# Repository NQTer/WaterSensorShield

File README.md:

# WaterSensorShield
RFM69 and ESP8266-01 enabled Water Level/Leak Detation Arduino Shield (Tested)

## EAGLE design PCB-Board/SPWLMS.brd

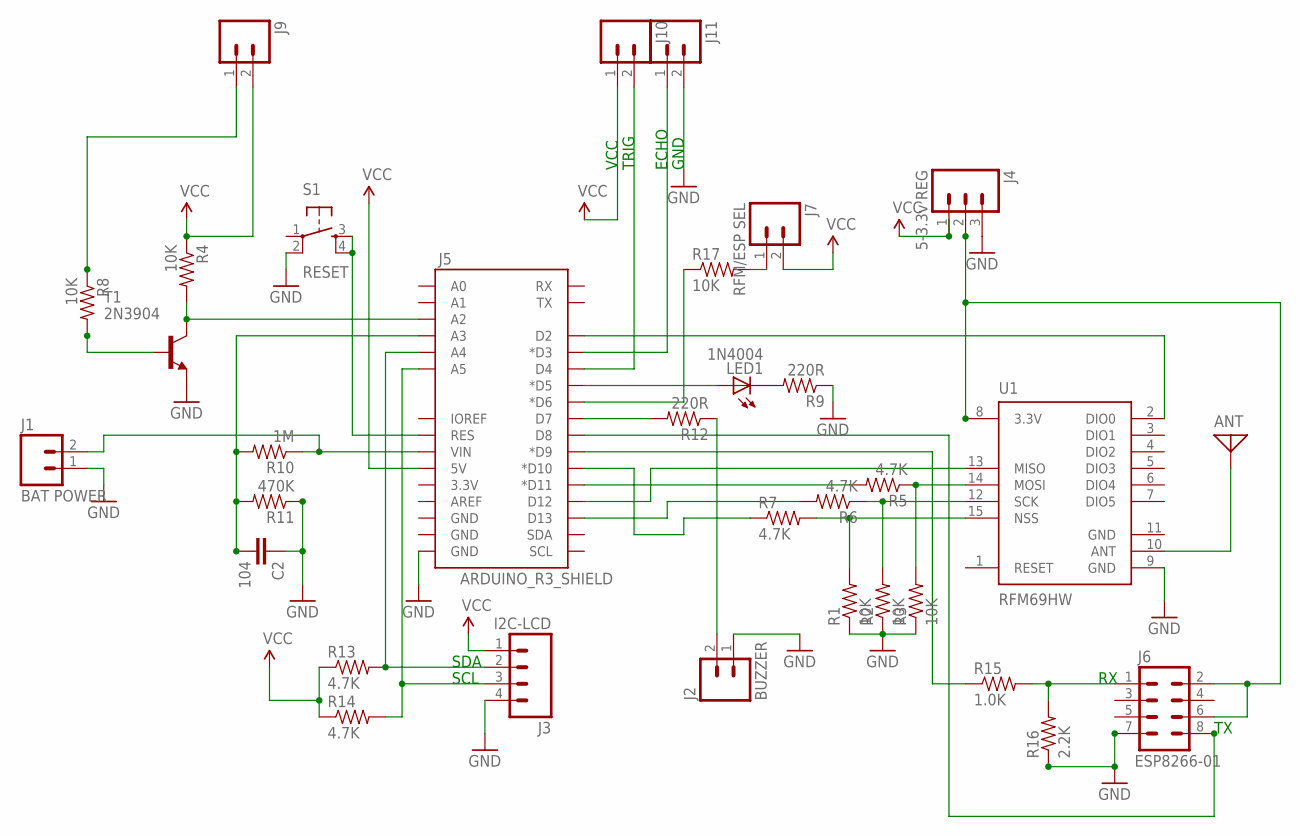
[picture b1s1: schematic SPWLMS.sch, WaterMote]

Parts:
ANT: ANTENNA; PAD-01
C2: 104; C2.5-4
J1: BAT POWER; 1X02
J2: BUZZER; 1X02
J3: I2C-LCD; 1X04_NO_SILK_ALL_ROUND
J4: 5-3.3v REG; 1X03_LOCK
J5: ARDUINO_R3_SHIELD; UNO_R3_SHIELD
J6: ESP8266-01; 2X4
J7: RFM/ESP SEL; 1X02
J9, J10, J11: M025MM; SCREWTERMINAL-5MM-2
LED1: 1N4004; LED5MM
R1, R2, R3, R4, R8, R17: 10K; AXIAL-0.4
R5, R6, R7, R13, R14: 4.7K; AXIAL-0.4
R9, R12: 220R; AXIAL-0.4
R10: 1M; AXIAL-0.4
R11: 470K; AXIAL-0.4
R15: 1.0K; AXIAL-0.4
R16: 2.2K; AXIAL-0.4
S1: RESET; TACTILE-PTH
T1: 2N3904; TO92
U1: RFM69HW; RFM69W-XXXS2

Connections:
GND: C2.1, J1.1, J2.1, J3.4, J4.3, J5.GND@0 (GND), J6.7, J11.2, R1.P$1 (1), R2.P$1 (1), R3.P$1 (1), R9.P$1 (1), R11.P$1 (1), R16.P$1 (1), S1.2, T1.3 (E), U1.9 (GND), U1.11 (GND)
unnamed: J5.D12, U1.13 (MISO)
unnamed: J5.D11 (*D11), R5.P$2 (2)
unnamed: R3.P$2 (2), R5.P$1 (1), U1.14 (MOSI)
unnamed: J5.D13, R6.P$2 (2)
unnamed: R2.P$2 (2), R6.P$1 (1), U1.12 (SCK)
unnamed: R1.P$2 (2), R7.P$2 (2), U1.15 (NSS)
unnamed: J5.D10 (*D10), R7.P$1 (1)
unnamed: J5.D5 (*D5), LED1.A
unnamed: J4.2, J6.2, J6.6, U1.8 (3.3V)
unnamed: J5.D2, U1.2 (DIO0)
unnamed: ANT.1, U1.10 (ANT)
unnamed: J5.A2, R4.P$2 (2), T1.1 (C)
unnamed: C2.2, J5.A3, R10.P$2 (2), R11.P$2 (2)
unnamed: R8.P$2 (2), T1.2 (B)
unnamed: J9.1, R8.P$1 (1)
unnamed: LED1.K (C), R9.P$2 (2)
unnamed: J3.2, J5.A4, R13.P$2 (2)
unnamed: J5.D4, J10.2
unnamed: J5.D3 (*D3), J11.1
unnamed: J1.2, J5.VIN, R10.P$1 (1)
unnamed: J5.D7, R12.P$2 (2)
unnamed: J2.2, R12.P$1 (1)
unnamed: J3.3, J5.A5, R14.P$2 (2)
unnamed: J5.RES, S1.3, S1.4
unnamed: J5.D9 (*D9), R15.P$1 (1)
unnamed: J6.1, R15.P$2 (2), R16.P$2 (2)
unnamed: J5.D8, J6.8
unnamed: J5.D6 (*D6), R17.P$1 (1)
unnamed: J7.1, R17.P$2 (2)
VCC: J3.1, J4.1, J5.5V, J7.2, J9.2, J10.1, R4.P$1 (1), R13.P$1 (1), R14.P$1 (1)

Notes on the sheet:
VCC
TRIG
ECHO
GND
SDA
SCL

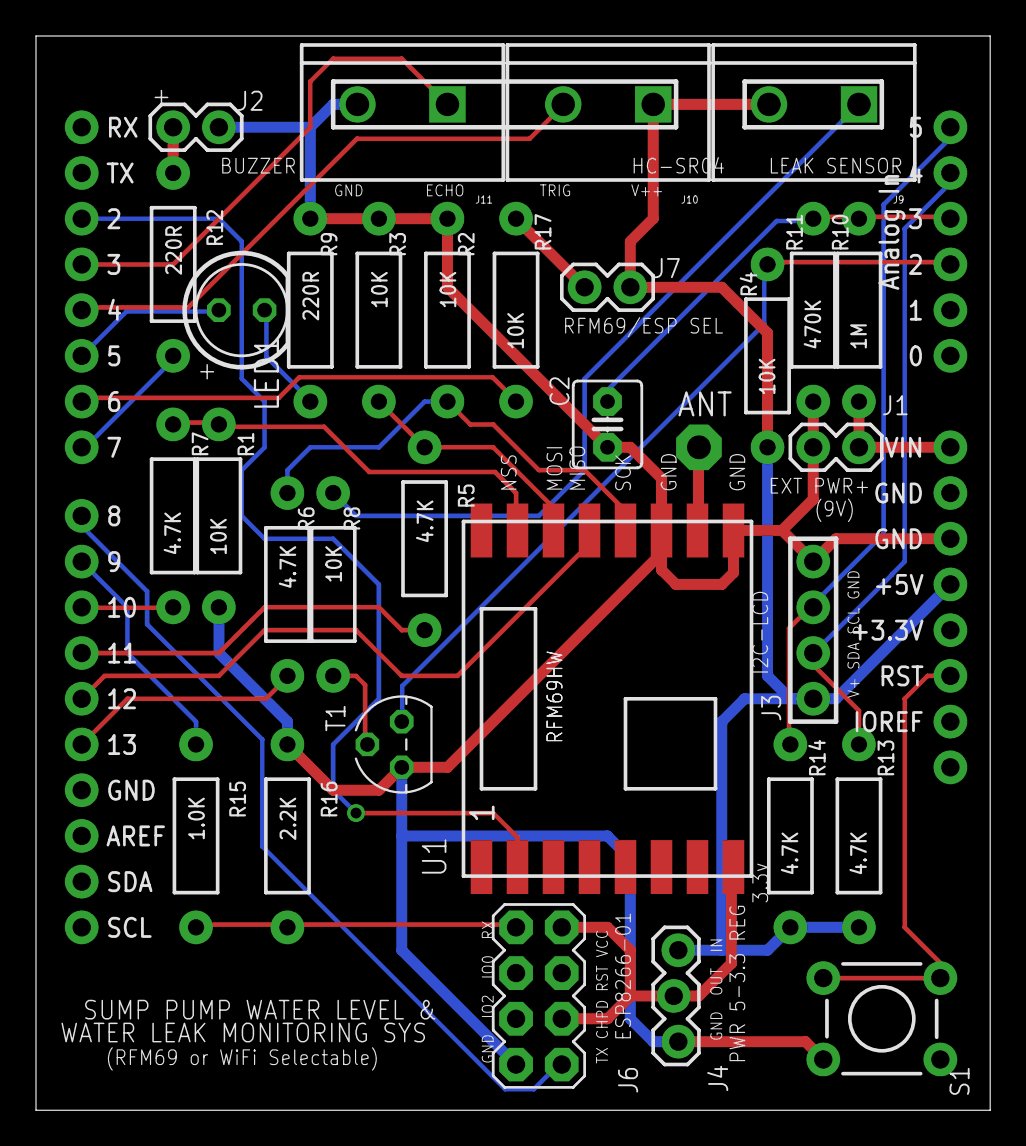
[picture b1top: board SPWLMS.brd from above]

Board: 2 copper layers, 53.0 x 59.7 mm, 33 parts (0 on the bottom side), 31 nets.

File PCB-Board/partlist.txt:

Partlist

Exported from SPWLMS.brd at 3/31/2016 9:46 PM

EAGLE Version 7.5.0 Copyright (c) 1988-2015 CadSoft

Assembly variant: 

Part     Value             Package                Library             Position (inch)       Orientation

ANT                        PAD-01                 discrete            (1.45 2.25)           R0
C2       104               C2.5-4                 capacitor-wima      (1.25 2.3)            R90
J1       BAT POWER         1X02                   SparkFun-Connectors (1.7 2.25)            R0
J2       BUZZER            1X02                   SparkFun-Connectors (0.4 2.95)            R180
J3       I2C-LCD           1X04_NO_SILK_ALL_ROUND SparkFun-Connectors (1.7 1.7)             R90
J4       5-3.3v REG        1X03_LOCK              SparkFun-Connectors (1.4 1.15)            R270
J5       ARDUINO_R3_SHIELD UNO_R3_SHIELD          SparkFun-Boards     (0 0.8)               R0
J6       ESP8266-01        2X4                    SparkFun-Connectors (1.1 1.05)            R270
J7       RFM/ESP SEL       1X02                   SparkFun-Connectors (1.2 2.6)             R0
J9                         SCREWTERMINAL-5MM-2    SparkFun-Connectors (1.8 3)               R180
J10                        SCREWTERMINAL-5MM-2    SparkFun-Connectors (1.35 3)              R180
J11                        SCREWTERMINAL-5MM-2    SparkFun-Connectors (0.9 3)               R180
LED1     1N4004            LED5MM                 led                 (0.45 2.55)           R0
R1       10K               AXIAL-0.4              SparkFun-Passives   (0.4 2.1)             R90
R2       10K               AXIAL-0.4              SparkFun-Passives   (0.9 2.55)            R270
R3       10K               AXIAL-0.4              SparkFun-Passives   (0.75 2.55)           R270
R4       10K               AXIAL-0.4              SparkFun-Passives   (1.6 2.45)            R90
R5       4.7K              AXIAL-0.4              SparkFun-Passives   (0.85 2.05)           R270
R6       4.7K              AXIAL-0.4              SparkFun-Passives   (0.55 1.95)           R270
R7       4.7K              AXIAL-0.4              SparkFun-Passives   (0.3 2.1)             R90
R8       10K               AXIAL-0.4              SparkFun-Passives   (0.65 1.95)           R270
R9       220R              AXIAL-0.4              SparkFun-Passives   (0.6 2.55)            R270
R10      1M                AXIAL-0.4              SparkFun-Passives   (1.8 2.55)            R90
R11      470K              AXIAL-0.4              SparkFun-Passives   (1.7 2.55)            R90
R12      220R              AXIAL-0.4              SparkFun-Passives   (0.3 2.65)            R270
R13      4.7K              AXIAL-0.4              SparkFun-Passives   (1.8 1.4)             R90
R14      4.7K              AXIAL-0.4              SparkFun-Passives   (1.65 1.4)            R90
R15      1.0K              AXIAL-0.4              SparkFun-Passives   (0.35 1.4)            R270
R16      2.2K              AXIAL-0.4              SparkFun-Passives   (0.55 1.4)            R270
R17      10K               AXIAL-0.4              SparkFun-Passives   (1.05 2.55)           R90
S1       RESET             TACTILE-PTH            SparkFun-Retired    (1.85 1)              R180
T1       2N3904            TO92                   transistor          (0.8 1.6)             R90
U1       RFM69HW           RFM69W-XXXS2           SparkFun-RF         (1.25 1.7)            R90

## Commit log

2016-04-28 Added files via upload
2016-08-27 Added sample source code
2016-08-27 Requirements for sample code

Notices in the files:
parts and their libraries:
SparkFun-Connectors: Licensing: Creative Commons ShareAlike 4.0 International - https://creativecommons.org/licenses/by-sa/4.0
